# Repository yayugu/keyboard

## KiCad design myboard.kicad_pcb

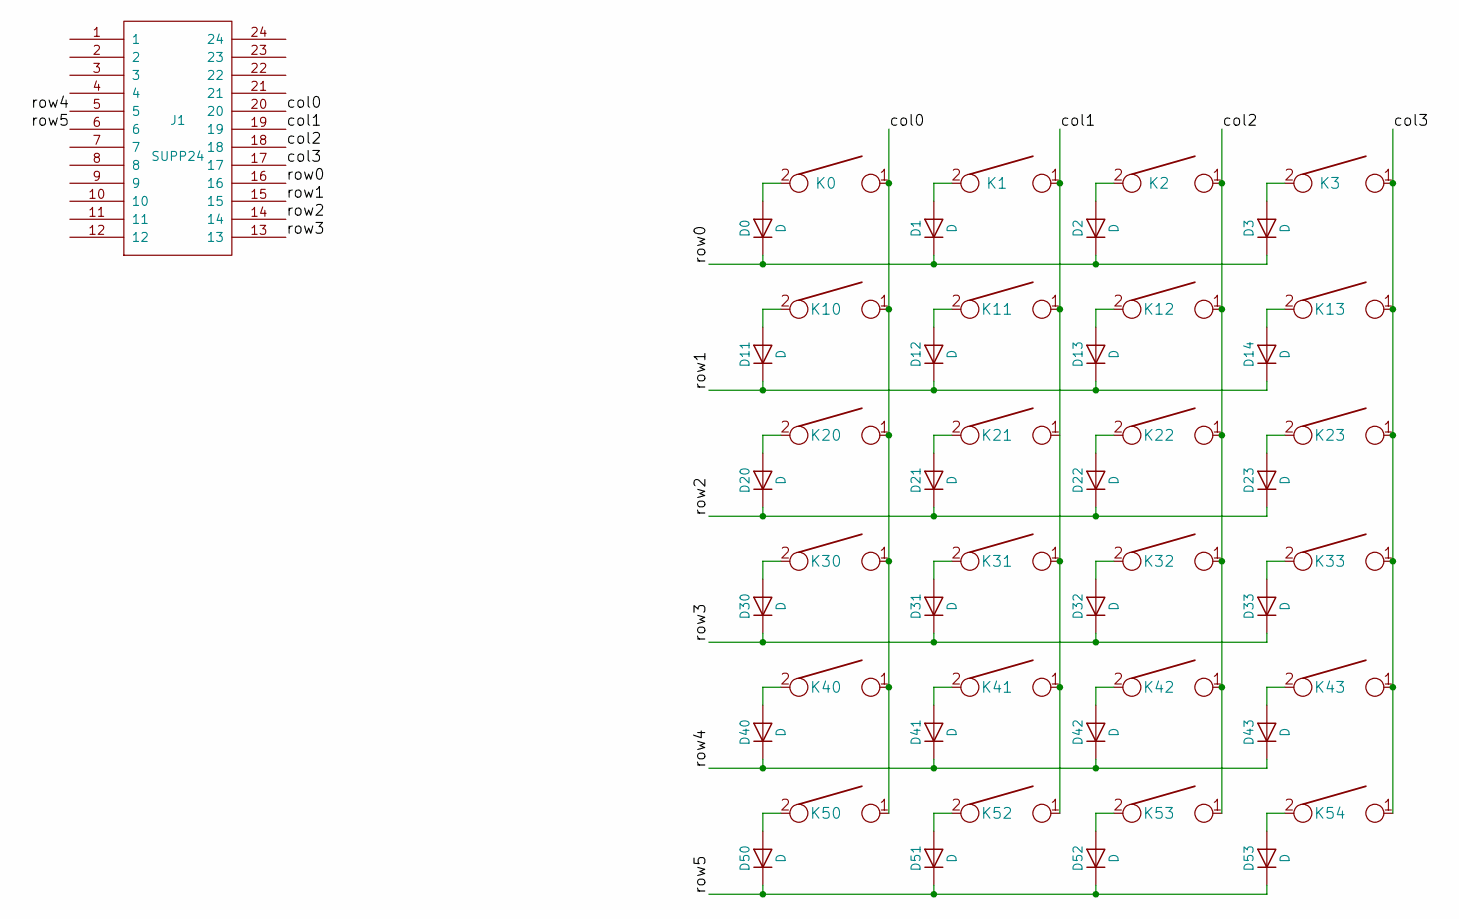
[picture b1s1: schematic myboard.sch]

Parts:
D0, D1, D2, D3, D11, D12, D13, D14, D20, D21, D22, D23, D30, D31, D32, D33, D40, D41, D42, D43, D50, D51, D52, D53: D; D_SOD123_axial
J1: SUPP24; Pro_Micro
K0, K1, K2, K3, K10, K11, K12, K13, K20, K21, K22, K23, K30, K31, K32, K33, K40, K41, K42, K43, K50, K52, K53, K54: KEYSW; Mx_Alps_100

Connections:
/col0: J1.20, K0.1, K10.1, K20.1, K30.1, K40.1, K50.1
/col1: J1.19, K1.1, K11.1, K31.1, K41.1, K52.1
/col2: J1.18, K2.1, K12.1, K22.1, K32.1, K42.1, K53.1
/col3: J1.17, K3.1, K13.1, K23.1, K33.1, K43.1, K54.1
/row0: D0.1 (K), D1.1 (K), D2.1 (K), D3.1 (K), J1.16
/row1: D11.1 (K), D12.1 (K), D13.1 (K), D14.1 (K), J1.15
/row2: D20.1 (K), D21.1 (K), D22.1 (K), D23.1 (K), J1.14
/row3: D30.1 (K), D31.1 (K), D32.1 (K), D33.1 (K), J1.13
/row4: D40.1 (K), D41.1 (K), D42.1 (K), D43.1 (K), J1.5
/row5: D50.1 (K), D51.1 (K), D52.1 (K), D53.1 (K), J1.6
unnamed: D0.2 (A), K0.2
unnamed: D1.2 (A), K1.2
unnamed: D2.2 (A), K2.2
unnamed: D3.2 (A), K3.2
unnamed: D11.2 (A), K10.2
unnamed: D12.2 (A), K11.2
unnamed: D13.2 (A), K12.2
unnamed: D14.2 (A), K13.2
unnamed: D20.2 (A), K20.2
unnamed: D21.2 (A), K21.2
unnamed: D22.2 (A), K22.2
unnamed: D23.2 (A), K23.2
unnamed: D30.2 (A), K30.2
unnamed: D31.2 (A), K31.2
unnamed: D32.2 (A), K32.2
unnamed: D33.2 (A), K33.2
unnamed: D40.2 (A), K40.2
unnamed: D41.2 (A), K41.2
unnamed: D42.2 (A), K42.2
unnamed: D43.2 (A), K43.2
unnamed: D50.2 (A), K50.2
unnamed: D51.2 (A), K52.2
unnamed: D52.2 (A), K53.2
unnamed: D53.2 (A), K54.2

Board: 2 copper layers, 49 parts (0 on the bottom side), 34 nets, no tracks yet.

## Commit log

2017-04-16 hoge
